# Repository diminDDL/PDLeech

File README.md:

# PDLeech
A USB-C board that fits in between the power supply and any PD target outputting constant 5V at a low current for powering or charging low power devices.

## Note
Current PCB with VBUS routing is bad, make trace thicker or re-do it as a pour.

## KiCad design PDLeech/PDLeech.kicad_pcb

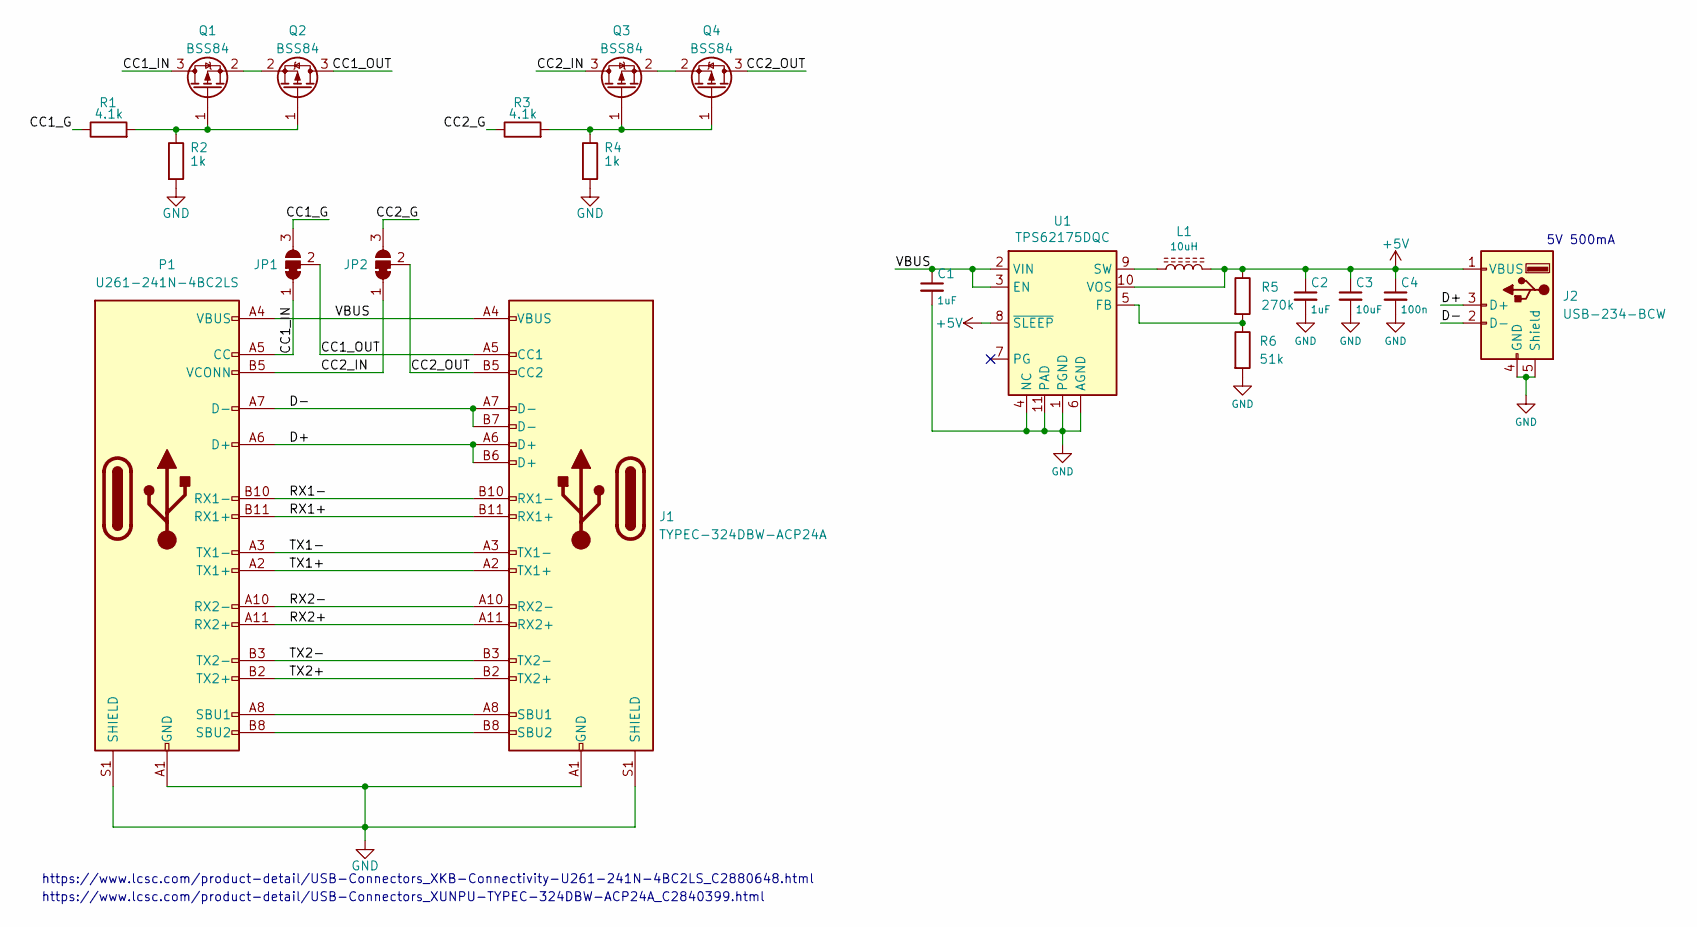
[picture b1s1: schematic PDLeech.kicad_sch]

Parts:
C1, C2: 1uF; C_0805_2012Metric_Pad1.18x1.45mm_HandSolder
C3: 10uF; C_0805_2012Metric_Pad1.18x1.45mm_HandSolder
C4: 100n; C_0805_2012Metric_Pad1.18x1.45mm_HandSolder
J1: TYPEC-324DBW-ACP24A; USB_C_Receptacle_Amphenol_12401548E4-2A
J2: USB-234-BCW; SAMTEC_USB-A-S-X-X-SM2
JP1, JP2: SolderJumper_3_Bridged12; SolderJumper-3_P1.3mm_Bridged12_RoundedPad1.0x1.5mm_NumberL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
L1: 10uH; L_4012
P1: U261-241N-4BC2LS; USB-C-SMD_XKB_U261-241N-4BC2LS
Q1, Q2, Q3, Q4: BSS84; SOT-23
R1, R3: 4.1k; R_0603_1608Metric_Pad0.98x0.95mm_HandSolder
R2, R4: 1k; R_0603_1608Metric_Pad0.98x0.95mm_HandSolder
R5: 270k; R_0603_1608Metric_Pad0.98x0.95mm_HandSolder
R6: 51k; R_0603_1608Metric_Pad0.98x0.95mm_HandSolder
U1: TPS62175DQC; WSON-10-1EP_2x3mm_P0.5mm_EP0.84x2.4mm

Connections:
+5V: C2.1, C3.1, C4.1, J2.1 (VBUS), L1.2, R5.1, U1.8 (~SLEEP), U1.10 (VOS)
/CC1_G: JP1.3 (B), R1.1
/CC1_IN: JP1.1 (A), P1.A5 (CC), Q1.3 (D)
/CC1_OUT: J1.A5 (CC1), JP1.2 (C), Q2.3 (D)
/CC2_G: JP2.3 (B), R3.1
/CC2_IN: JP2.1 (A), P1.B5 (VCONN), Q3.3 (D)
/CC2_OUT: J1.B5 (CC2), JP2.2 (C), Q4.3 (D)
/D+: J1.A6 (D+), J1.B6 (D+), J2.3 (D+), P1.A6 (D+)
/D-: J1.A7 (D-), J1.B7 (D-), J2.2 (D-), P1.A7 (D-)
/RX1+: J1.B11 (RX1+), P1.B11 (RX1+)
/RX1-: J1.B10 (RX1-), P1.B10 (RX1-)
/RX2+: J1.A11 (RX2+), P1.A11 (RX2+)
/RX2-: J1.A10 (RX2-), P1.A10 (RX2-)
/TX1+: J1.A2 (TX1+), P1.A2 (TX1+)
/TX1-: J1.A3 (TX1-), P1.A3 (TX1-)
/TX2+: J1.B2 (TX2+), P1.B2 (TX2+)
/TX2-: J1.B3 (TX2-), P1.B3 (TX2-)
/VBUS: C1.1, J1.A4 (VBUS), J1.A9 (VBUS), J1.B4 (VBUS), J1.B9 (VBUS), P1.A4 (VBUS), P1.A9 (VBUS), P1.B4 (VBUS), P1.B9 (VBUS), U1.2 (VIN), U1.3 (EN)
GND: C1.2, C2.2, C3.2, C4.2, J1.A1 (GND), J1.A12 (GND), J1.B1 (GND), J1.B12 (GND), J1.S1 (SHIELD), J2.4 (GND), J2.5 (Shield), P1.A1 (GND), P1.A12 (GND), P1.B1 (GND), P1.B12 (GND), P1.S1 (SHIELD), R2.2, R4.2, R6.2, U1.1 (PGND), U1.4 (NC), U1.6 (AGND), U1.11 (PAD)
unnamed: J1.A8 (SBU1), P1.A8 (SBU1)
unnamed: J1.B8 (SBU2), P1.B8 (SBU2)
unnamed: L1.1, U1.9 (SW)
unnamed: Q1.1 (G), Q2.1 (G), R1.2, R2.1
unnamed: Q1.2 (S), Q2.2 (S)
unnamed: Q3.1 (G), Q4.1 (G), R3.2, R4.1
unnamed: Q3.2 (S), Q4.2 (S)
unnamed: R5.2, R6.1, U1.5 (FB)

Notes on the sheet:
https://www.lcsc.com/product-detail/USB-Connectors_XKB-Connectivity-U261-241N-4BC2LS_C2880648.html
https://www.lcsc.com/product-detail/USB-Connectors_XUNPU-TYPEC-324DBW-ACP24A_C2840399.html
5V 500mA

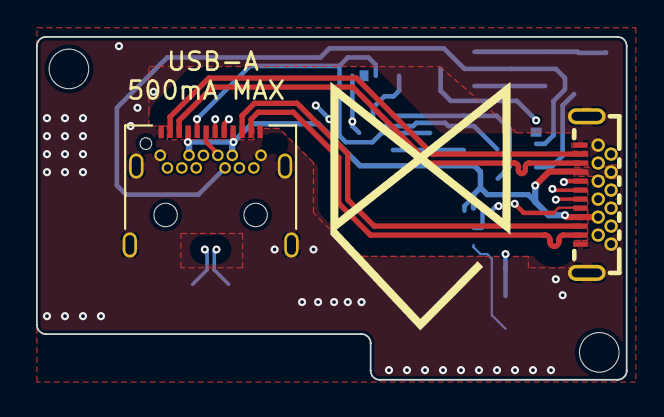
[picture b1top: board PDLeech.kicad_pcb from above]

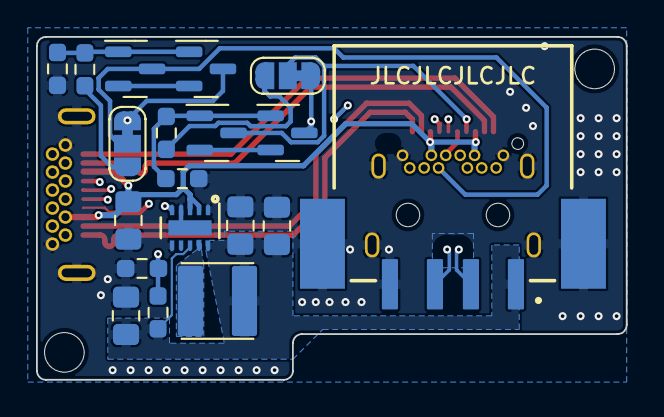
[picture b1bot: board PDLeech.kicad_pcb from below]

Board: 4 copper layers, 32.8 x 19.1 mm, 21 parts (19 on the bottom side), 27 nets.

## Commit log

2023-01-29 added schematic
2023-01-29 schematic finished
2023-01-31 updated schematic
2023-02-01 added some footprtints
2023-02-07 selected all footprints
2023-02-09 schematic complete and footprints selected
2023-02-09 rough layout complete
2023-02-09 layout done
2023-02-09 added gerbers
